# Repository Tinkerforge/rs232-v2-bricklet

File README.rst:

RS232 Bricklet 2.0
==================

This repository contains the firmware source code and the hardware design
files. The documentation generator configs can be found at
https://github.com/Tinkerforge/generators

Repository Content
------------------

software/:
 * examples/: Examples for all supported languages
 * build/: Compiled files
 * src/: Source code of firmware
 * Makefile: Makefile to build project

hardware/:
 * Contains KiCad project files and additionally schematics as PDF

datasheets/:
 * Contains datasheets for sensors and complex ICs that are used

Hardware
--------

The hardware is designed with the open source EDA Suite KiCad
(http://www.kicad.org). Before you are able to open the files,
you have to install the Tinkerforge kicad-libraries
(https://github.com/Tinkerforge/kicad-libraries). You can either clone
them directly in hardware/ or clone them in a separate folder and
symlink them into hardware/
(ln -s kicad_path/kicad-libraries project_path/hardware). After that you
can open the .pro file in hardware/ with KiCad and from there view and
modify the schematics and the PCB layout.

Software
--------

If you want to do your own Brick/Bricklet firmware development we highly
recommend that you use our build environment setup script and read the
tutorial (https://www.tinkerforge.com/en/doc/Tutorials/Tutorial_Build_Environment/Tutorial.html).

To compile the C code we recommend you to install the newest GNU Arm Embedded
Toolchain (https://launchpad.net/gcc-arm-embedded/+download).
You also need to install bricklib2 (https://github.com/Tinkerforge/bricklib2).

You can either clone it directly in software/src/ or clone it in a
separate folder and symlink it into software/src/
(ln -s bricklib_path/bricklib2 project_path/software/src/). Finally make sure to
have CMake installed (http://www.cmake.org/cmake/resources/software.html).

After that you can build the firmware by invoking make in software/.
The firmware (.zbin) can then be found in software/build/ and uploaded
with brickv (click button "Flashing" on start screen).

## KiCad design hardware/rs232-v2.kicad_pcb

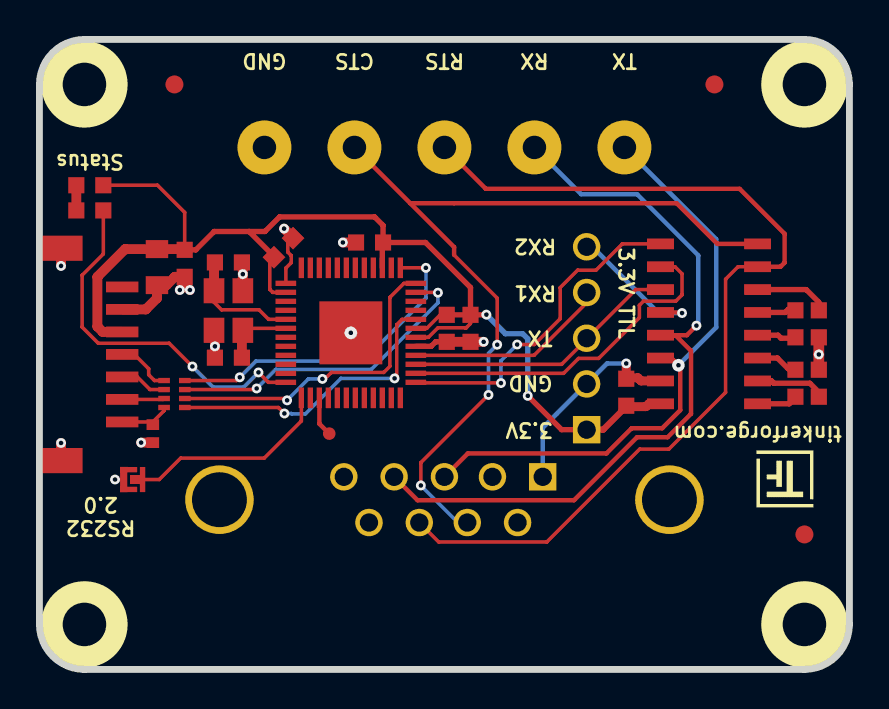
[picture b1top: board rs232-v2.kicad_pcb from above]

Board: 2 copper layers, 45.0 x 35.0 mm, 35 parts (0 on the bottom side), 31 nets.

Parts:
C1: 220pF; C0402F
C2, C5: 10pF; C0603F
C3: 10uF; C0805
C4: 1uF; C0603F
C6, C7, C8, C9, C10, C11, C12, C13: 100nF; C0603F
C14: 220nF; C0603F
D1: blue; D0603F
Fiducial_Mark: VAL**; Fiducial_Mark
Fiducial_Mark#2, Fiducial_Mark#3: VAL**; Fiducial_Mark
J1: DB9; SUB09-EU
P1: CON-SENSOR; CON-SENSOR2
P2: CONN_5; AKL_5_5
P3: CONN_5; pin_array_5x1
P4: BOOT; SolderJumper
P5: BOOT; DEBUG_PAD
R2: 1k; R0603F
RP1: 82; 4X0402
U1: XMC1403; QFN48-EP2
U3: SP3232EBCN; SOIC16
U4, U5, U6, U7: DRILL; DRILL_NP
VAL: CE_5mm
VAL#2: WEEE_7mm
X1: 16MHz; CRYSTAL_3225

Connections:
GND: C1.1, C2.1, C3.1, C4.1, C5.1, C6.1, C9.1, C10.1, C11.1, C12.1, C13.1, C14.1, J1.1, P1.2, P1.EP, P2.1, P3.2, P4.1, U1.17, U1.37, U1.EP, U3.15, X1.3
unnamed: C1.2, P1.7, RP1.4
unnamed: C2.2, U1.41, X1.2
unnamed: C5.2, U1.42, X1.1
unnamed: C7.1, U3.1
unnamed: C7.2, U3.3
unnamed: C8.1, U3.4
unnamed: C8.2, U3.5
unnamed: C10.2, U3.2
unnamed: C11.2, U3.6
unnamed: D1.2, R2.2
unnamed: J1.3, P2.5, U3.14
unnamed: J1.4, P2.4, U3.13
unnamed: J1.7, P2.2, U3.8
unnamed: J1.8, P2.3, U3.7
unnamed: P1.4, RP1.1
unnamed: P1.5, RP1.2
unnamed: P1.6, RP1.3
unnamed: P3.5, U3.12
unnamed: P4.2, U1.1
unnamed: P5.1, U1.3
unnamed: R2.1, U1.48
RX: P3.4, U1.16
S-CLK: RP1.7, U1.23
S-CS: RP1.8, U1.25
S-MISO: RP1.5, U1.20
S-MOSI: RP1.6, U1.24
TX: P3.3, U1.15, U3.11
VCC: C3.2, C4.2, C6.2, C9.2, C12.2, C13.2, C14.2, D1.1, P1.3, P3.1, U1.18, U1.19, U1.27, U1.38, U3.16
nCTS: U1.13, U3.9
nRTS: U1.14, U3.10

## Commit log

2018-01-16 Add datasheet
2018-01-16 Add readme and license
2018-01-16 Add initial schematic
2018-01-16 Remove cache lib
2018-01-16 Add pcb layout
2018-01-16 Minor adjustments
2018-01-19 remove 0 ohm resitor in crystal circuitry
2018-02-20 Add .gitignore
2018-02-20 Cleanup KiCad libraries config
    Ensure LibDir=kicad-libraries and LibName1=tinkerforge.
    Remove special library.
2018-03-07 Remove unused datasheet
2018-03-07 Add initial stub of RS232 V2 firmware
2018-03-15 fix status text
2018-03-15 drc check
2018-03-15 Partial firmware implementation
2018-03-16 Functional firmware implementation. Yet to implement:
    1. Flow control
    2. Tick based RX FIFO drain
2018-03-20 Firmware implementation
2018-03-20 Disable logging
2018-03-27 specify processor
2018-04-16 Add 3d information (final)
2018-04-23 Add 3d model (*.FCStd & *.step)
2018-05-04 Rename files
2018-05-04 Add schematic PDF
2018-05-29 Define flash size to be 64KB
2018-05-29 Add examples
2018-06-07 Update changelog for initial release
2018-06-08 javascript: Fix string splitting
2018-06-11 Fix 3d model
2018-06-18 Change capacitor footprint(s) to C0402F
2018-06-28 Fix readme
2018-07-11 Add Makefile with docker support
2018-07-11 Update directory structure and build instructions
2018-07-11 Remove obsolete generate_makefile scripts
2018-07-17 examples: Remove unnecessary length printing
2018-07-17 examples: Fix string to char array logic
2018-07-17 delphi: Use PChar instead of PAnsiChar
    With PAnsiChar the message "test" will be printed as "t e " in Delphi XE.
2018-10-04 Increase version for new release (changes in bricklib2)
2018-10-04 Add rev to changelog
2018-11-06 Add rust examples
2018-11-07 rust: Accept host names for ip connection, fix naming inconsistencies
2018-11-07 rust: Rename callback receivers.
2018-12-14 Add go examples.
2018-12-18 go: Change import path.
2018-12-18 go: Change import path again.
2018-12-20 rust: Reformat examples.
2019-01-24 mqtt: Add examples.
2019-01-24 mqtt: Remove executable bit in example permissions.
2019-01-24 go: Minor example fixes.
2019-08-22 c: Adapt to bindings changes
2019-12-03 examples: Improve wording of comment
2020-01-14 examples: Use python3 input by default.
2020-02-13 Don't reset stream in getter if callback is enabled and vice versa.
2020-02-14 Add available callback. Used for openHAB.
2020-02-14 Change available callback to frame readable.
    This now also reports the number of readable frames not readable bytes.
2020-02-25 Add get_frame_readable_callback_configuration.
2020-02-25 Mutually exclude read/frame_readable callbacks.
2020-02-28 Append to changelog.
2020-02-28 Add commit ref to changelog.
2020-03-18 Whitespace
2020-03-18 rust: Update to new skeleton
2020-03-26 Configure TX pin high during configuration
    otherwise there can be glitches on TX line if configuration changes.
2020-03-26 Add ref for 2.0.4
2020-04-07 examples: rust: Always block when calling bindings functions.
2020-04-07 examples: rust: Fix merge conflict.
2020-08-19 Add uc examples.
2020-08-25 uc: Adapt example to new skeleton
2020-08-27 uc: Fix warnings.
2020-08-31 uc: Use fixed-with placeholders in format strings.
2020-09-02 uc: Add example driver note.
2021-06-23 fix library, define xmc1403 as minimum instead of xmc1404
2021-06-23 Use XMC1403 as minimum requirement
2021-06-23 Add ref for 2.0.5
2021-10-25 Update KiCad link
    https://www.kicad.org/blog/2021/10/Avoid-links-to-former-kicad-domain/
2022-04-19 examples: uc: Rename TF_HalContext to TF_HAL.
2022-04-26 uc: Adapt to current bindings
2022-04-26 uc: Remove unused include
2022-07-06 Add license files.

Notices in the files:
hardware/rs232-v2.kicad_pcb:
Licensed under CERN OHL v.1.1
Copyright (©) 2018, L.Lauer
Copyright Tinkerforge GmbH 2018.
This documentation describes Open Hardware and is licensed under the
CERN OHL v. 1.1.
